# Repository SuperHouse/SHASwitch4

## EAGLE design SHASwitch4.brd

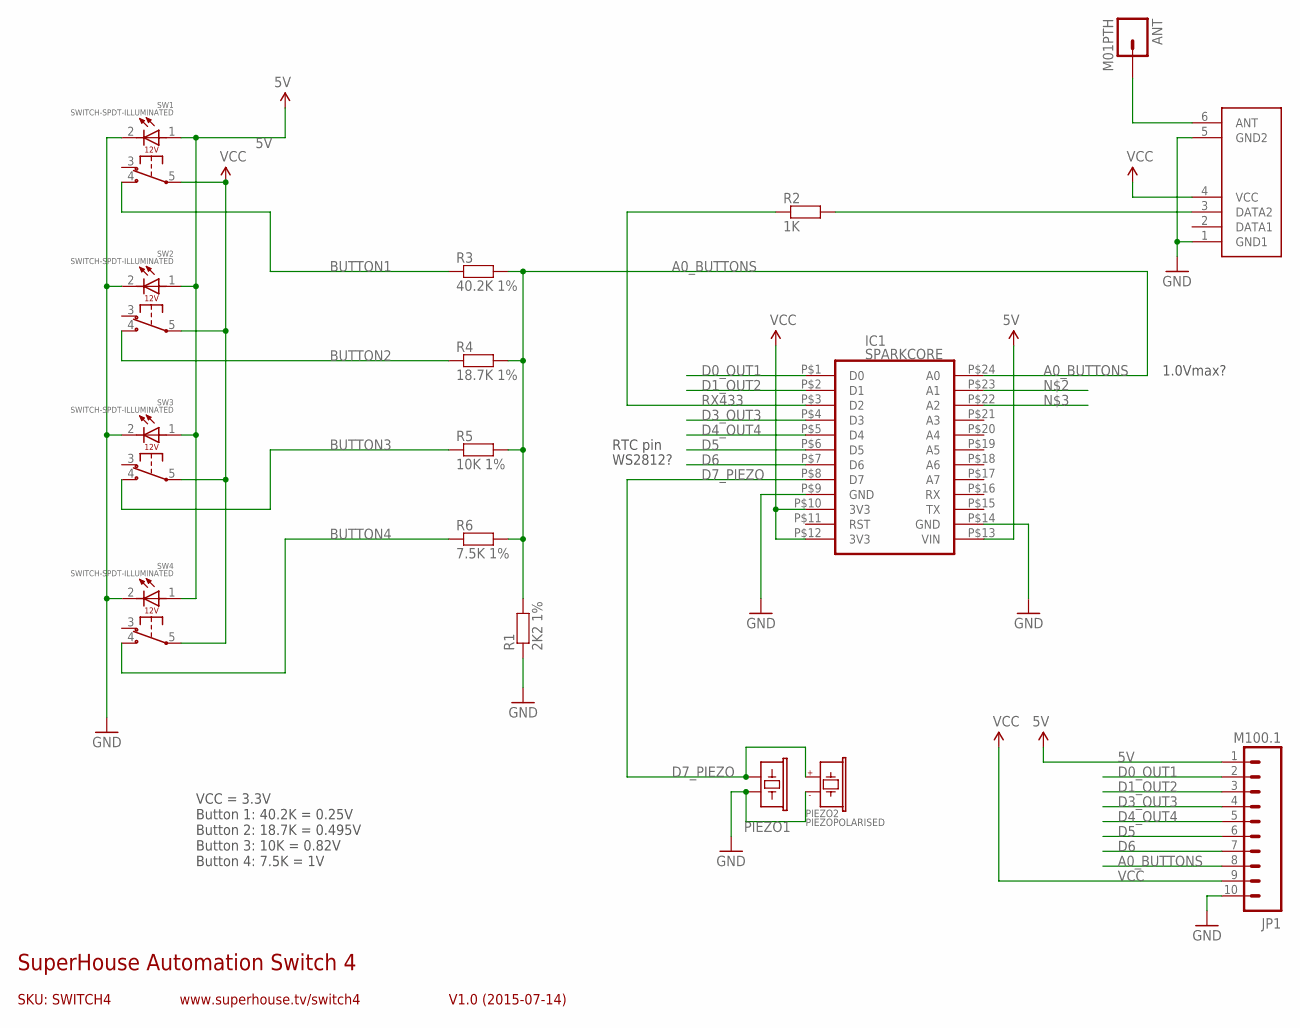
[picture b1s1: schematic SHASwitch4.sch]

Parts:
ANT: M01PTH; 1X01
IC1: SPARKCORE
IC3: RXB1; RX-B1-SHORT-FLAT
JP1: M100.1; 1X10
PIEZO1: BUZZERSMD12X12; BUZZER-12X12-SMT
PIEZO2: PIEZOPOLARISED; PIEZO12MMWIDEPOLARISED
R1: 2K2 1%; 0603
R2: 1K; 0603
R3: 40.2K 1%; 0603
R4: 18.7K 1%; 0603
R5: 10K 1%; 0603
R6: 7.5K 1%; 0603
SW1, SW2, SW3, SW4: SWITCH-SPDT-ILLUMINATED

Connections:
5V: IC1.P$13 (VIN), JP1.1, SW1.1 (+), SW2.1 (+), SW3.1 (+), SW4.1 (+)
A0_BUTTONS: IC1.P$24 (A0), JP1.8, R1.2, R3.2, R4.2, R5.2, R6.2
BUTTON1: R3.1, SW1.4 (NO)
BUTTON2: R4.1, SW2.4 (NO)
BUTTON3: R5.1, SW3.4 (NO)
BUTTON4: R6.1, SW4.4 (NO)
D0_OUT1: IC1.P$1 (D0), JP1.2
D1_OUT2: IC1.P$2 (D1), JP1.3
D3_OUT3: IC1.P$4 (D3), JP1.4
D4_OUT4: IC1.P$5 (D4), JP1.5
D5: IC1.P$6 (D5), JP1.6
D6: IC1.P$7 (D6), JP1.7
D7_PIEZO: IC1.P$8 (D7), PIEZO1.1, PIEZO2.1 (+)
GND: IC1.P$9 (GND), IC1.P$14 (GND), IC3.1 (GND1), IC3.5 (GND2), JP1.10, PIEZO1.2, PIEZO2.2 (-), R1.1, SW1.2 (-), SW2.2 (-), SW3.2 (-), SW4.2 (-)
unnamed: ANT.1, IC3.6 (ANT)
unnamed: IC3.3 (DATA2), R2.2
RX433: IC1.P$3 (D2), R2.1
VCC: IC1.P$10 (3V3), IC1.P$12 (3V3), IC3.4 (VCC), JP1.9, SW1.5 (COM), SW2.5 (COM), SW3.5 (COM), SW4.5 (COM)

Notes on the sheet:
SKU: SWITCH4
SuperHouse Automation Switch 4
V1.0 (2015-07-14)
www.superhouse.tv/switch4
RTC pin
1.0Vmax?
VCC = 3.3V Button 1: 40.2K = 0.25V Button 2: 18.7K = 0.495V Button 3: 10K = 0.82V Button 4: 7.5K = 1V
WS2812?

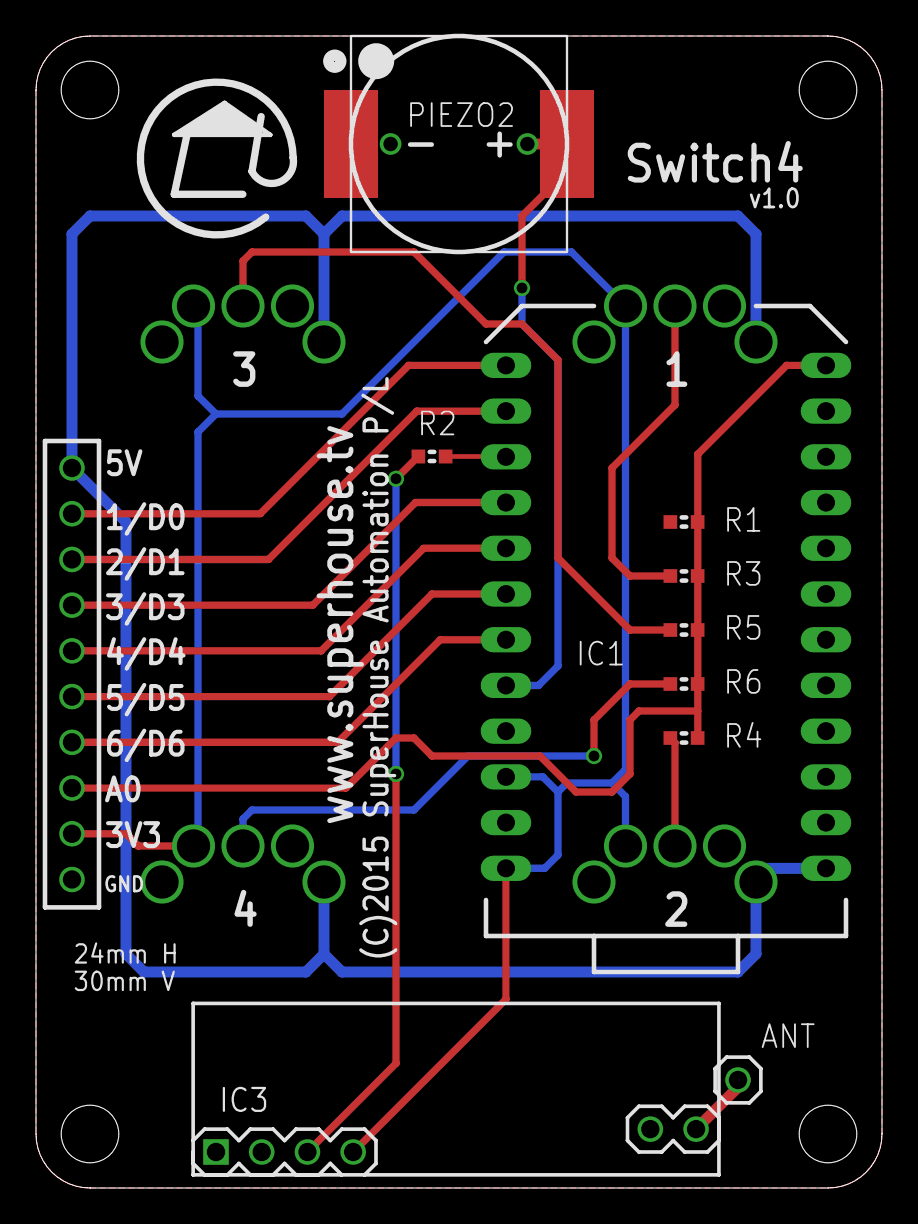
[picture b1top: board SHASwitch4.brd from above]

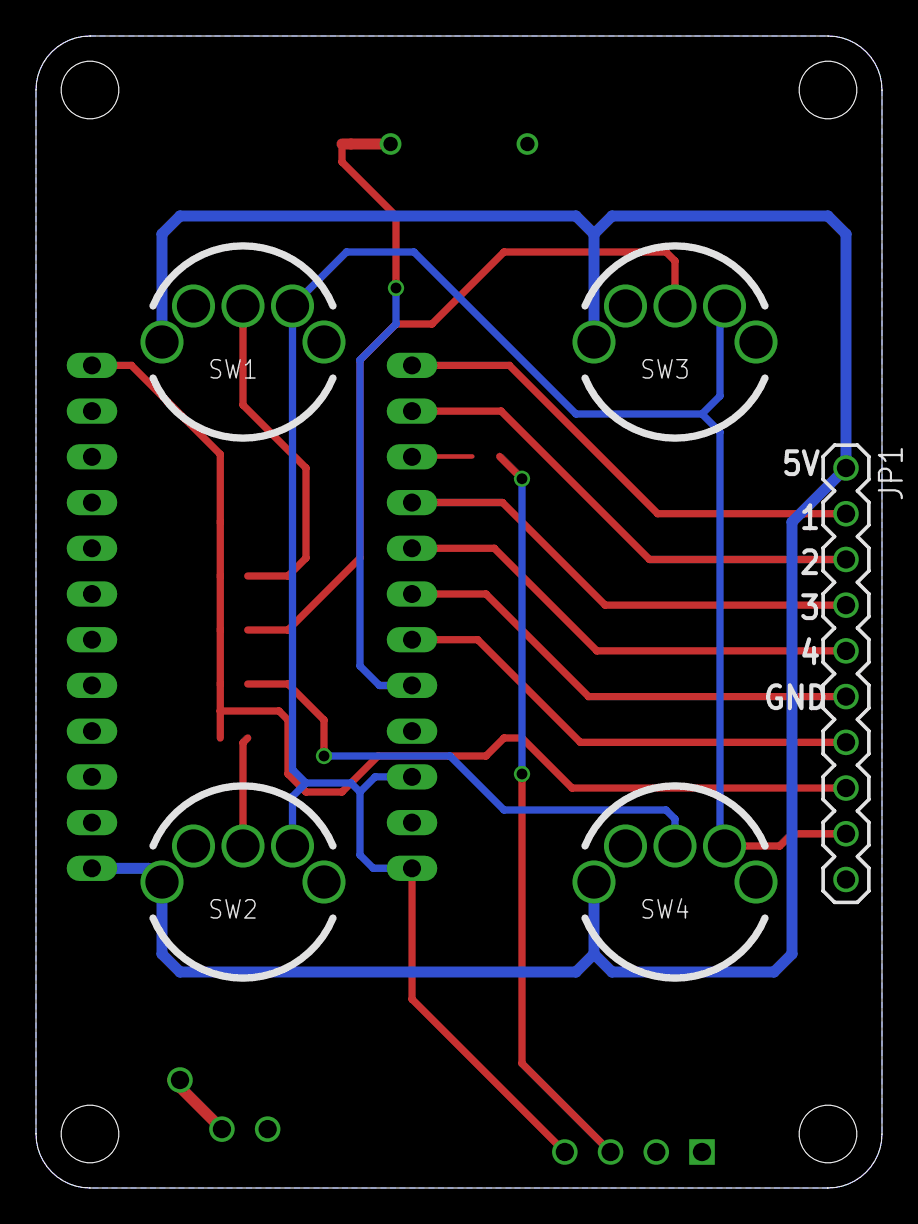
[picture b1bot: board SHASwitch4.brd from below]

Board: 2 copper layers, 47.0 x 64.0 mm, 16 parts (5 on the bottom side), 18 nets.

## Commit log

2019-04-24 Initial project import

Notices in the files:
SHASwitch4.brd:
(C)2015 SuperHouse Automation P/L
parts and their libraries:
freetronics-original: Licensing: CC v3.0 Share-Alike You are welcome to use this library for commercial purposes.
